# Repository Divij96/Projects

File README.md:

# Projects
## ROS project avalanche rescue
### Search and Rescue avalanche scenario (Mission), Autonomous Systems
- The project was implemented in C++ using ROS packages. Visualization was done in Unity environment and Rviz. <br />

Task: fly over the avalanche and locate victims. Work packages included:- <br />
-  realistic sensor models for avalanche beacon (noise & capabilities)
-  mission planning
-  adaptive trajectory generation
-  location report

## Scara Robot
### Design and build-up of a 4 DoF SCARA like robot (3+1gripper), Intelligent machine design lab
- Mechanical models were designed using Autodesk inventor and built using 3dprinters
- The PCBs were designed using the Autodesk Eagle. They were later on manufactured
and soldered
- Each joint had an Absolute position encoder, a Torque sensor, a BLDC motor, a
gearbox, and a pair of Cross-Roller-Bearings. A master Linux PC with EtherCAT was
used for communication with the joint slaves
- The low-level control was implemented on the Microcontroller chip using C. A highlevel
control was implemented in MATLAB. EtherLab was used as a communication
interface
- The CDTM (Center for Digital Technology Management) supported us regarding the
team communication and project management aspects

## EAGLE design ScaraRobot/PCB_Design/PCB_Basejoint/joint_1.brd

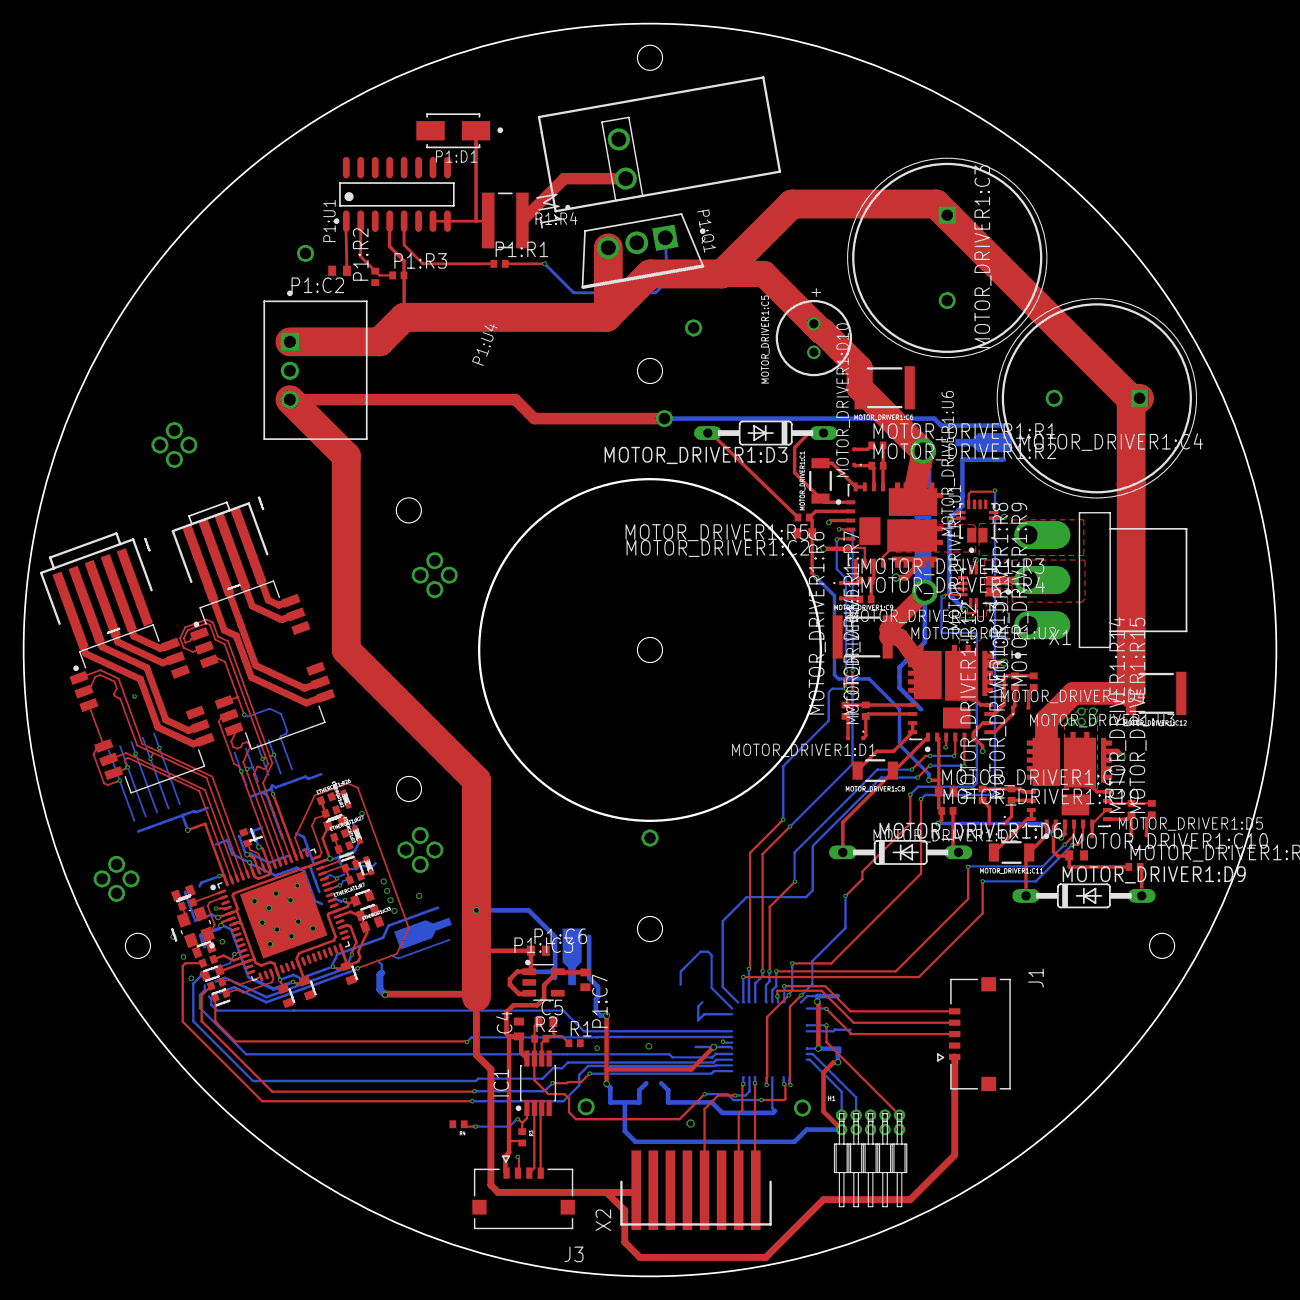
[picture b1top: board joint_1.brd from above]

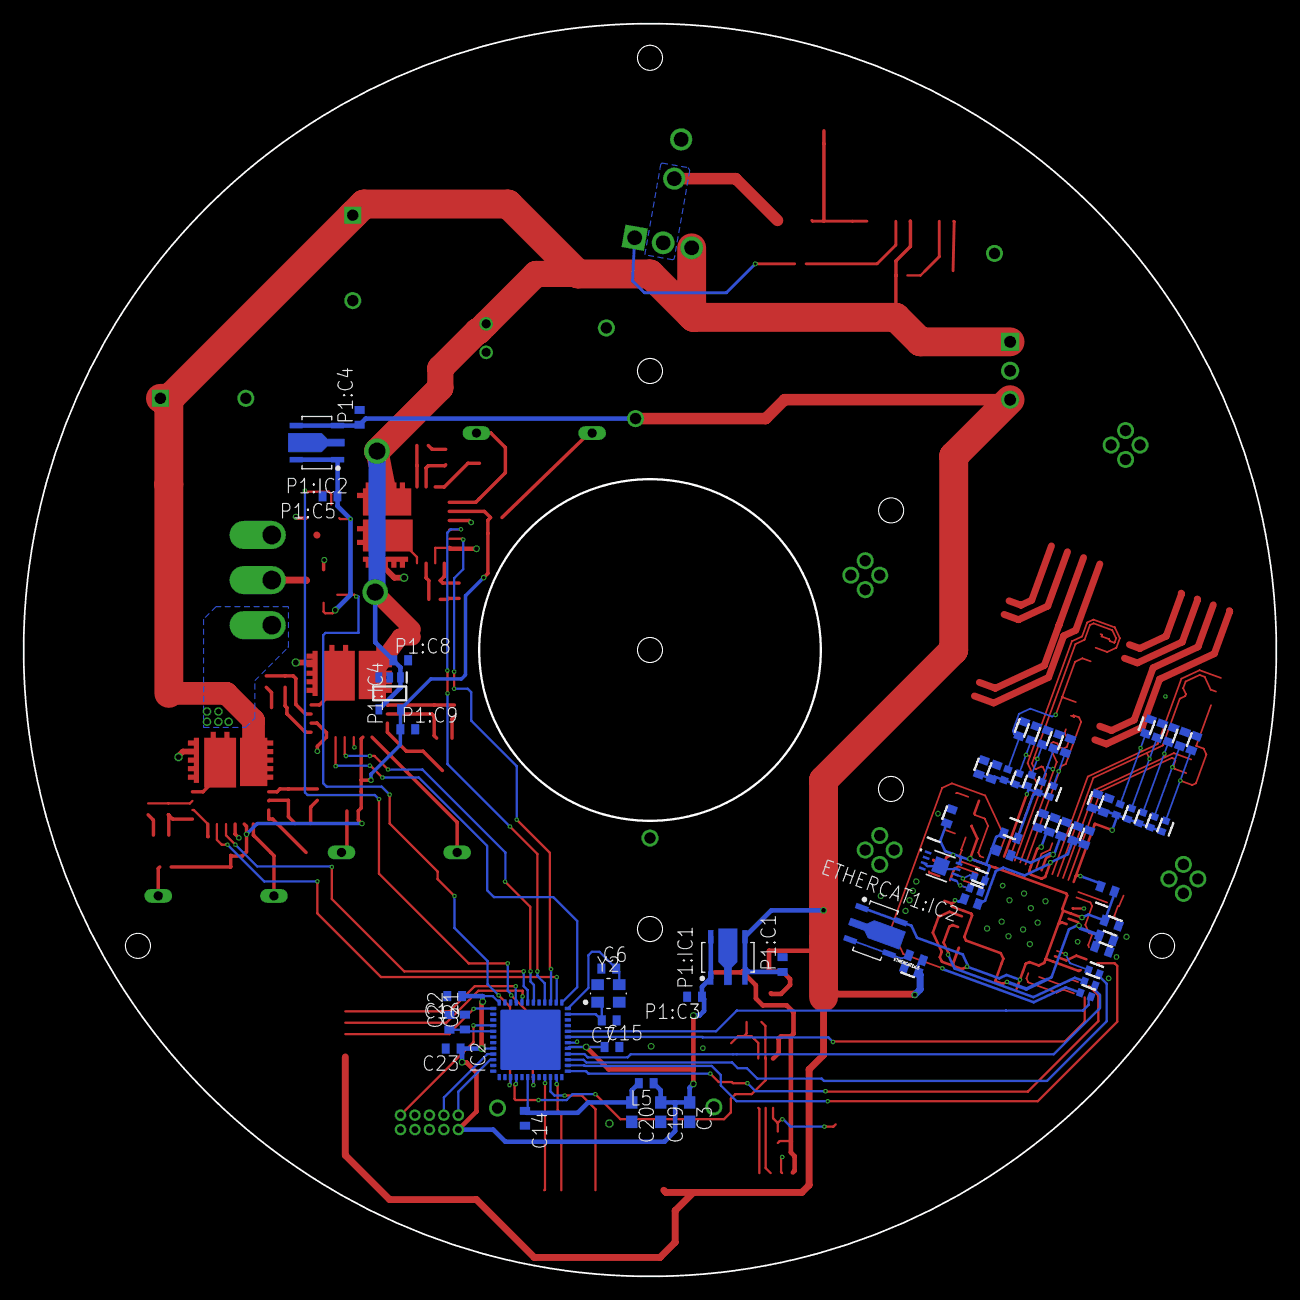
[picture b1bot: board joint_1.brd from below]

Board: 2 copper layers, 110.0 x 110.0 mm, 166 parts (69 on the bottom side), 120 nets.

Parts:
C3, C19, C20: 10uF/10V; C0603
C4, C14, C15, C16, C23: 100nF; C0402
C5: GCM1555C1H102FA16; C0402
C6, C7: GCM1555C1H100JA16; C0402
C21: GCM155R71C104JA55; C0402
C22: GRM155C80J475MEAAD; C0402
ETHERCAT1:C1, ETHERCAT1:C3, ETHERCAT1:C6, ETHERCAT1:C8, ETHERCAT1:C16: 1u; C0402
ETHERCAT1:C2, ETHERCAT1:C4, ETHERCAT1:C5, ETHERCAT1:C7, ETHERCAT1:C9, ETHERCAT1:C10, ETHERCAT1:C11, ETHERCAT1:C12, ETHERCAT1:C13, ETHERCAT1:C14, ETHERCAT1:C15, ETHERCAT1:C18, ETHERCAT1:C19, ETHERCAT1:C22: 100n; C0402
ETHERCAT1:C17: 470p; C0402
ETHERCAT1:C20, ETHERCAT1:C21: 18p; C0402
ETHERCAT1:C23, ETHERCAT1:C24, ETHERCAT1:C25, ETHERCAT1:C26, ETHERCAT1:C27, ETHERCAT1:C28, ETHERCAT1:C29, ETHERCAT1:C30: GCM1555C1H100JA16; C0402
ETHERCAT1:C31, ETHERCAT1:C32: 22n; C0402
ETHERCAT1:C33: GRM155C80J106ME11D; C0402
ETHERCAT1:C66: 1uF; C0402
ETHERCAT1:D1, ETHERCAT1:D2, ETHERCAT1:D3: QBLP595-IG; LED0402
ETHERCAT1:IC1: CAT24C512IGT3HU5; UDFN8
ETHERCAT1:IC2: RP115H331B-T1-FE; SOT-89-5
ETHERCAT1:L1, ETHERCAT1:L2, ETHERCAT1:L3, ETHERCAT1:L4, ETHERCAT1:L5: BLM15EG221SH1D; BEAD0402
ETHERCAT1:R1, ETHERCAT1:R16, ETHERCAT1:R17: 0R; R0402
ETHERCAT1:R2: 12k1; R0402
ETHERCAT1:R4, ETHERCAT1:R5: 4k7; R0402
ETHERCAT1:R6, ETHERCAT1:R24, ETHERCAT1:R25: 10k; R0402
ETHERCAT1:R7, ETHERCAT1:R26, ETHERCAT1:R27: RL0402FR-7W10KL; R0402
ETHERCAT1:R8, ETHERCAT1:R9, ETHERCAT1:R10, ETHERCAT1:R11, ETHERCAT1:R12, ETHERCAT1:R13, ETHERCAT1:R14, ETHERCAT1:R15: 49R9; R0402
ETHERCAT1:R18, ETHERCAT1:R19, ETHERCAT1:R20, ETHERCAT1:R21, ETHERCAT1:R22, ETHERCAT1:R23: 100; R0402
ETHERCAT1:T1, ETHERCAT1:T2: 749020100; SOIC127P965X533-16-TRAFO
ETHERCAT1:U1: LAN9252/ML; QFN64-T600
ETHERCAT1:X1: 87438-0443; 87438-04
ETHERCAT1:X3: 87438-0543; 87438-05
ETHERCAT1:Y1: ECX-2236
H1: 20021112-00010T4LF; 20021112-00010
IC1: MAX4208AUA+T; USOP8
IC2: ATSAMD51G18A-MUT; QFN48
J1: 5037630591; MOLEX_5037630591
J3: 5037630491; MOLEX_5037630491
L5: BLM15EG221SH1D; BEAD0402
M1: PST1,3/2-3,5; 1945096
MOTOR_DRIVER1:C1, MOTOR_DRIVER1:C8, MOTOR_DRIVER1:C11: 10 µF; WCAP-CSGP_1206_H1.6
MOTOR_DRIVER1:C2, MOTOR_DRIVER1:C7, MOTOR_DRIVER1:C10: 10u 25V; C0402
MOTOR_DRIVER1:C3, MOTOR_DRIVER1:C4: MAL219091105E3; CAPPRD750W80D1650H2700
MOTOR_DRIVER1:C5: 220 µF; WCAP-ATG8_6.3X11(DXL)
MOTOR_DRIVER1:C6, MOTOR_DRIVER1:C9, MOTOR_DRIVER1:C12: 470000pF; WCAP-CSMH_1812_H2.0
MOTOR_DRIVER1:D1, MOTOR_DRIVER1:D2, MOTOR_DRIVER1:D4, MOTOR_DRIVER1:D5, MOTOR_DRIVER1:D10, MOTOR_DRIVER1:D11: INFINEON_BAS3005A-02VINFINEON_BAS3005A-02V_0_0; INFINEON_BAS3005A-02V_0
MOTOR_DRIVER1:D3, MOTOR_DRIVER1:D6, MOTOR_DRIVER1:D9: BAV21; DO35-10
MOTOR_DRIVER1:R1, MOTOR_DRIVER1:R4, MOTOR_DRIVER1:R6, MOTOR_DRIVER1:R9, MOTOR_DRIVER1:R12, MOTOR_DRIVER1:R15: 27; R0402
MOTOR_DRIVER1:R2, MOTOR_DRIVER1:R3, MOTOR_DRIVER1:R7, MOTOR_DRIVER1:R8, MOTOR_DRIVER1:R13, MOTOR_DRIVER1:R14: 100; R0402
MOTOR_DRIVER1:R5, MOTOR_DRIVER1:R10, MOTOR_DRIVER1:R16: 5.1; R0402
MOTOR_DRIVER1:U1, MOTOR_DRIVER1:U2, MOTOR_DRIVER1:U3: IRSM005-800MHINFINEON_IRSM005-800MH_0_0; INFINEON_IRSM005-800MH_0
MOTOR_DRIVER1:U6, MOTOR_DRIVER1:U7: ALLEGRO_MICROSYSTEMS_LLC_ACS70331EESATR-005B3ALLE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; ALLEGRO_MICROSYSTEMS_LLC_ACS70331EESATR-005B3_0
P1:C1, P1:C3, P1:C4, P1:C5, P1:C6, P1:C8, P1:C9: GCM155C71A105KE38D; C0402
P1:C2: GCM155R71C104JA55; C0402
P1:C7: GRM155C80J225KE95D; C0402
P1:D1: DIODES_SMAT70A-13-FDIODES_SMAT70A-13-F_0_0; DIODES_SMAT70A-13-F_0
P1:IC1, P1:IC2: RP115H331B-T1-FE; SOT-89-5
P1:IC3: AP2204K-5.0TRG1; SOT-23-5
P1:IC4: XC6701AF02MR-G; SOT95P280X130-5N
P1:Q1: INFINEON_IRF640NPBFINFINEON_IRF640NPBF_0_0; INFINEON_IRF640NPBF_0
P1:R1: 10; R0402
P1:R2: 4.99k; R0402
P1:R3: 118k; R0402
P1:R4: VISHAY_CRCW12181K00FKEKVISHAY_CRCW12181K00FKEK_0_0; VISHAY_CRCW12181K00FKEK_0
P1:U1: LINEAR_TECHNOLOGY_LT4356HS-3#PBFLINEAR_TECHNOLOGY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; LINEAR_TECHNOLOGY_LT4356HS-3#PBF_0
P1:U4: RECOM_R-78E5.0-1.0RECOM_R-78E5.0-1.0_0_0; RECOM_R-78E5.0-1.0_0
R1: Rg; R0402
R2: Rg2; R0402
R3, R4: RT0402FRE07100KL; R0402
U$1: PTDA1,5/2-PH-3,5; 1725107
X1: B3PS-VH(LF)(SN)
X2: 87438-0843; 87438-08
Y2: ECX-2236

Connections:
3V3_CURRENT: MOTOR_DRIVER1:U6.12, MOTOR_DRIVER1:U7.12, P1:C5.1, P1:IC2.1, P1:IC2.5
3V3_MICRO: C3.1, C15.1, C16.1, C19.1, C23.1, H1.1, IC2.17, IC2.36, IC2.44, L5.1, P1:C3.1, P1:IC1.1, P1:IC1.5
5V_TORQUE: C4.1, IC1.8, J3.1, P1:C7.1, P1:IC3.5, R3.2
+5V: ETHERCAT1:C66.1, ETHERCAT1:L5.1, J1.1, P1:C1.1, P1:C4.1, P1:C6.1, P1:IC1.3, P1:IC1.4, P1:IC2.3, P1:IC2.4, P1:IC3.1, P1:IC3.3, P1:U4.3, X2.1
+15V: MOTOR_DRIVER1:C2.1, MOTOR_DRIVER1:C7.1, MOTOR_DRIVER1:C10.1, MOTOR_DRIVER1:R5.1, MOTOR_DRIVER1:R10.1, MOTOR_DRIVER1:R16.1, MOTOR_DRIVER1:U1.2, MOTOR_DRIVER1:U2.2, MOTOR_DRIVER1:U3.2, P1:C9.1, P1:IC4.5
+24V: MOTOR_DRIVER1:C3.1, MOTOR_DRIVER1:C4.1, MOTOR_DRIVER1:C5.1, MOTOR_DRIVER1:C6.2, MOTOR_DRIVER1:C9.2, MOTOR_DRIVER1:C12.2, MOTOR_DRIVER1:U1.18-19-20-21-22-23, MOTOR_DRIVER1:U2.18-19-20-21-22-23, MOTOR_DRIVER1:U3.18-19-20-21-22-23, P1:C8.1, P1:IC4.1, P1:IC4.4, P1:Q1.3, P1:R3.2, P1:U1.4, P1:U4.1
CURRENT_A: IC2.3, MOTOR_DRIVER1:U7.10
CURRENT_B: IC2.7, MOTOR_DRIVER1:U6.10
ECAT_CS: ETHERCAT1:R19.2, IC2.20
ECAT_DATA2: ETHERCAT1:R21.2, IC2.15
ECAT_DATA3: ETHERCAT1:R20.2, IC2.16
ECAT_MISO: ETHERCAT1:R22.2, IC2.14
ECAT_MOSI: ETHERCAT1:R23.2, IC2.13
ECAT_SCK: ETHERCAT1:R18.2, IC2.19
ENA: IC2.27, MOTOR_DRIVER1:U1.5
ENB: IC2.25, MOTOR_DRIVER1:U2.5
ENC: IC2.26, MOTOR_DRIVER1:U3.5
ETHERCAT1:#MISO: ETHERCAT1:R22.1, ETHERCAT1:U1.13
ETHERCAT1:#MOSI: ETHERCAT1:R23.1, ETHERCAT1:U1.17
ETHERCAT1:#SCK: ETHERCAT1:R18.1, ETHERCAT1:U1.19
ETHERCAT1:#SCS#: ETHERCAT1:R19.1, ETHERCAT1:U1.50
ETHERCAT1:#SQI2: ETHERCAT1:R21.1, ETHERCAT1:U1.12
ETHERCAT1:#SQI3: ETHERCAT1:R20.1, ETHERCAT1:U1.35
ETHERCAT1:+3V3: ETHERCAT1:C10.1, ETHERCAT1:C11.1, ETHERCAT1:C12.1, ETHERCAT1:C13.1, ETHERCAT1:C14.1, ETHERCAT1:C15.1, ETHERCAT1:C22.1, ETHERCAT1:C33.1, ETHERCAT1:D1.2, ETHERCAT1:IC1.8, ETHERCAT1:IC2.1, ETHERCAT1:IC2.5, ETHERCAT1:L1.1, ETHERCAT1:L2.1, ETHERCAT1:L3.1, ETHERCAT1:R4.2, ETHERCAT1:R5.2, ETHERCAT1:R6.2, ETHERCAT1:U1.5, ETHERCAT1:U1.7, ETHERCAT1:U1.14, ETHERCAT1:U1.20, ETHERCAT1:U1.32, ETHERCAT1:U1.37, ETHERCAT1:U1.47
ETHERCAT1:CT1: ETHERCAT1:C31.1, ETHERCAT1:R16.1, ETHERCAT1:T1.3, ETHERCAT1:T1.6
ETHERCAT1:CT2: ETHERCAT1:C32.1, ETHERCAT1:R17.1, ETHERCAT1:T2.3, ETHERCAT1:T2.6
ETHERCAT1:GPIO0: ETHERCAT1:R24.2, ETHERCAT1:R26.1, ETHERCAT1:U1.48
ETHERCAT1:GPIO1: ETHERCAT1:R25.2, ETHERCAT1:R27.1, ETHERCAT1:U1.46
ETHERCAT1:GPIO2: ETHERCAT1:R6.1, ETHERCAT1:R7.2, ETHERCAT1:U1.45
ETHERCAT1:I2C_SCL: ETHERCAT1:IC1.6, ETHERCAT1:R4.1, ETHERCAT1:U1.43
ETHERCAT1:I2C_SDA: ETHERCAT1:IC1.5, ETHERCAT1:R5.1, ETHERCAT1:U1.42
ETHERCAT1:IN_RX_N: ETHERCAT1:T1.9, ETHERCAT1:X1.4
ETHERCAT1:IN_RX_P: ETHERCAT1:T1.10, ETHERCAT1:X1.3
ETHERCAT1:IN_TX_N: ETHERCAT1:T1.15, ETHERCAT1:X1.2
ETHERCAT1:IN_TX_P: ETHERCAT1:T1.16, ETHERCAT1:X1.1
ETHERCAT1:N$1: ETHERCAT1:D2.2, ETHERCAT1:R26.2
ETHERCAT1:N$2: ETHERCAT1:D3.2, ETHERCAT1:R27.2
ETHERCAT1:N$3: ETHERCAT1:IC2.3, ETHERCAT1:IC2.4, ETHERCAT1:L5.2
ETHERCAT1:N$15: ETHERCAT1:D1.1, ETHERCAT1:R7.1
ETHERCAT1:OSCI: ETHERCAT1:R1.2, ETHERCAT1:U1.1
ETHERCAT1:OSCI1: ETHERCAT1:C20.2, ETHERCAT1:R1.1, ETHERCAT1:Y1.3
ETHERCAT1:OSCO: ETHERCAT1:C21.2, ETHERCAT1:U1.2, ETHERCAT1:Y1.1
ETHERCAT1:OUT_RX_N: ETHERCAT1:T2.9, ETHERCAT1:X3.5
ETHERCAT1:OUT_RX_P: ETHERCAT1:T2.10, ETHERCAT1:X3.4
ETHERCAT1:OUT_TX_N: ETHERCAT1:T2.15, ETHERCAT1:X3.3
ETHERCAT1:OUT_TX_P: ETHERCAT1:T2.16, ETHERCAT1:X3.2
ETHERCAT1:RBIAS: ETHERCAT1:R2.2, ETHERCAT1:U1.57
ETHERCAT1:RXA_N: ETHERCAT1:C24.1, ETHERCAT1:R10.1, ETHERCAT1:T1.8, ETHERCAT1:U1.54
ETHERCAT1:RXA_P: ETHERCAT1:C23.1, ETHERCAT1:R11.1, ETHERCAT1:T1.7, ETHERCAT1:U1.55
ETHERCAT1:RXB_N: ETHERCAT1:C28.1, ETHERCAT1:R14.1, ETHERCAT1:T2.2, ETHERCAT1:U1.61
ETHERCAT1:RXB_P: ETHERCAT1:C27.1, ETHERCAT1:R15.1, ETHERCAT1:T2.1, ETHERCAT1:U1.60
ETHERCAT1:TXA_N: ETHERCAT1:C26.1, ETHERCAT1:R8.1, ETHERCAT1:T1.2, ETHERCAT1:U1.52
ETHERCAT1:TXA_P: ETHERCAT1:C25.1, ETHERCAT1:R9.1, ETHERCAT1:T1.1, ETHERCAT1:U1.53
ETHERCAT1:TXB_N: ETHERCAT1:C30.1, ETHERCAT1:R12.1, ETHERCAT1:T2.8, ETHERCAT1:U1.63
ETHERCAT1:TXB_P: ETHERCAT1:C29.1, ETHERCAT1:R13.1, ETHERCAT1:T2.7, ETHERCAT1:U1.62
ETHERCAT1:VDD: ETHERCAT1:C16.1, ETHERCAT1:C17.1, ETHERCAT1:C18.1, ETHERCAT1:C19.1, ETHERCAT1:L4.1, ETHERCAT1:U1.6, ETHERCAT1:U1.24, ETHERCAT1:U1.38
ETHERCAT1:VDD12TX: ETHERCAT1:C6.1, ETHERCAT1:C7.1, ETHERCAT1:C8.1, ETHERCAT1:C9.1, ETHERCAT1:L4.2, ETHERCAT1:U1.56, ETHERCAT1:U1.59
ETHERCAT1:VDD33BIAS: ETHERCAT1:C5.1, ETHERCAT1:L3.2, ETHERCAT1:U1.58
ETHERCAT1:VDD33TXRX1: ETHERCAT1:C1.1, ETHERCAT1:C2.1, ETHERCAT1:L1.2, ETHERCAT1:R8.2, ETHERCAT1:R9.2, ETHERCAT1:R10.2, ETHERCAT1:R11.2, ETHERCAT1:R16.2, ETHERCAT1:U1.51
ETHERCAT1:VDD33TXRX2: ETHERCAT1:C3.1, ETHERCAT1:C4.1, ETHERCAT1:L2.2, ETHERCAT1:R12.2, ETHERCAT1:R13.2, ETHERCAT1:R14.2, ETHERCAT1:R15.2, ETHERCAT1:R17.2, ETHERCAT1:U1.64
GND: C3.2, C4.2, C6.1, C7.1, C14.2, C15.2, C16.2, C19.2, C20.2, C21.2, C22.2, C23.2, ETHERCAT1:C1.2, ETHERCAT1:C2.2, ETHERCAT1:C3.2, ETHERCAT1:C4.2, ETHERCAT1:C5.2, ETHERCAT1:C6.2, ETHERCAT1:C7.2, ETHERCAT1:C8.2, ETHERCAT1:C9.2, ETHERCAT1:C10.2, ETHERCAT1:C11.2, ETHERCAT1:C12.2, ETHERCAT1:C13.2, ETHERCAT1:C14.2, ETHERCAT1:C15.2, ETHERCAT1:C16.2, ETHERCAT1:C17.2, ETHERCAT1:C18.2, ETHERCAT1:C19.2, ETHERCAT1:C20.1, ETHERCAT1:C21.1, ETHERCAT1:C22.2, ETHERCAT1:C23.2, ETHERCAT1:C24.2, ETHERCAT1:C25.2, ETHERCAT1:C26.2, ETHERCAT1:C27.2, ETHERCAT1:C28.2, ETHERCAT1:C29.2, ETHERCAT1:C30.2, ETHERCAT1:C31.2, ETHERCAT1:C32.2, ETHERCAT1:C33.2, ETHERCAT1:C66.2, ETHERCAT1:D2.1, ETHERCAT1:D3.1, ETHERCAT1:IC1.1, ETHERCAT1:IC1.2, ETHERCAT1:IC1.3, ETHERCAT1:IC1.4, ETHERCAT1:IC1.7, ETHERCAT1:IC1.9, ETHERCAT1:IC2.2, ETHERCAT1:R2.1, ETHERCAT1:R24.1, ETHERCAT1:R25.1, ETHERCAT1:U1.4, ETHERCAT1:U1.8, ETHERCAT1:U1.9, ETHERCAT1:U1.10, ETHERCAT1:U1.41, ETHERCAT1:U1.65, ETHERCAT1:Y1.2, ETHERCAT1:Y1.4, H1.3, H1.5, IC1.4, IC1.5, IC2.5, IC2.18, IC2.35, IC2.42, J1.2, J3.2, M1.2, MOTOR_DRIVER1:C2.2, MOTOR_DRIVER1:C3.2, MOTOR_DRIVER1:C4.2, MOTOR_DRIVER1:C5.2, MOTOR_DRIVER1:C6.1, MOTOR_DRIVER1:C7.2, MOTOR_DRIVER1:C9.1, MOTOR_DRIVER1:C10.2, MOTOR_DRIVER1:C12.1, MOTOR_DRIVER1:U1.3, MOTOR_DRIVER1:U1.6, MOTOR_DRIVER1:U1.8, MOTOR_DRIVER1:U1.11-12-13-14-15, MOTOR_DRIVER1:U2.3, MOTOR_DRIVER1:U2.6, MOTOR_DRIVER1:U2.8, MOTOR_DRIVER1:U2.11-12-13-14-15, MOTOR_DRIVER1:U3.3, MOTOR_DRIVER1:U3.6, MOTOR_DRIVER1:U3.8, MOTOR_DRIVER1:U3.11-12-13-14-15, MOTOR_DRIVER1:U6.5, MOTOR_DRIVER1:U7.5, P1:C1.2, P1:C2.2, P1:C3.2, P1:C4.2, P1:C5.2, P1:C6.2, P1:C7.2, P1:C8.2, P1:C9.2, P1:D1.2, P1:IC1.2, P1:IC2.2, P1:IC3.2, P1:IC4.2, P1:R2.1, P1:U1.12, P1:U4.2, R1.2, R4.2, X2.2, Y2.2, Y2.4
HALL_A: IC2.33, J1.5
HALL_B: IC2.32, J1.4
HALL_C: IC2.37, J1.3
INA: IC2.28, MOTOR_DRIVER1:U1.4
INB: IC2.30, MOTOR_DRIVER1:U2.4
INC: IC2.31, MOTOR_DRIVER1:U3.4
MOTOR_DRIVER1:N$1: MOTOR_DRIVER1:R1.2, MOTOR_DRIVER1:R2.2, MOTOR_DRIVER1:U1.24
MOTOR_DRIVER1:N$2: MOTOR_DRIVER1:D10.2, MOTOR_DRIVER1:R1.1
MOTOR_DRIVER1:N$3: MOTOR_DRIVER1:D10.1, MOTOR_DRIVER1:R2.1, MOTOR_DRIVER1:U1.25
MOTOR_DRIVER1:N$4: MOTOR_DRIVER1:R6.2, MOTOR_DRIVER1:R7.2, MOTOR_DRIVER1:U2.24
MOTOR_DRIVER1:N$5: MOTOR_DRIVER1:R3.2, MOTOR_DRIVER1:R4.2, MOTOR_DRIVER1:U1.9
MOTOR_DRIVER1:N$6: MOTOR_DRIVER1:D11.2, MOTOR_DRIVER1:R4.1
MOTOR_DRIVER1:N$7: MOTOR_DRIVER1:D11.1, MOTOR_DRIVER1:R3.1, MOTOR_DRIVER1:U1.7
MOTOR_DRIVER1:N$8: MOTOR_DRIVER1:C1.2, MOTOR_DRIVER1:U1.26, MOTOR_DRIVER1:U1.27
MOTOR_DRIVER1:N$9: MOTOR_DRIVER1:C1.1, MOTOR_DRIVER1:D3.C, MOTOR_DRIVER1:U1.1
MOTOR_DRIVER1:N$10: MOTOR_DRIVER1:D3.A, MOTOR_DRIVER1:R5.2
MOTOR_DRIVER1:N$12: MOTOR_DRIVER1:D1.2, MOTOR_DRIVER1:R6.1
MOTOR_DRIVER1:N$13: MOTOR_DRIVER1:D1.1, MOTOR_DRIVER1:R7.1, MOTOR_DRIVER1:U2.25
MOTOR_DRIVER1:N$14: MOTOR_DRIVER1:R8.2, MOTOR_DRIVER1:R9.2, MOTOR_DRIVER1:U2.9
MOTOR_DRIVER1:N$15: MOTOR_DRIVER1:D4.2, MOTOR_DRIVER1:R9.1
MOTOR_DRIVER1:N$16: MOTOR_DRIVER1:D4.1, MOTOR_DRIVER1:R8.1, MOTOR_DRIVER1:U2.7
MOTOR_DRIVER1:N$17: MOTOR_DRIVER1:C8.2, MOTOR_DRIVER1:U2.26, MOTOR_DRIVER1:U2.27
MOTOR_DRIVER1:N$18: MOTOR_DRIVER1:C8.1, MOTOR_DRIVER1:D6.C, MOTOR_DRIVER1:U2.1
MOTOR_DRIVER1:N$19: MOTOR_DRIVER1:D6.A, MOTOR_DRIVER1:R10.2
MOTOR_DRIVER1:N$21: MOTOR_DRIVER1:R12.2, MOTOR_DRIVER1:R13.2, MOTOR_DRIVER1:U3.24
MOTOR_DRIVER1:N$22: MOTOR_DRIVER1:D2.2, MOTOR_DRIVER1:R12.1
MOTOR_DRIVER1:N$23: MOTOR_DRIVER1:D2.1, MOTOR_DRIVER1:R13.1, MOTOR_DRIVER1:U3.25
MOTOR_DRIVER1:N$24: MOTOR_DRIVER1:R14.2, MOTOR_DRIVER1:R15.2, MOTOR_DRIVER1:U3.9
MOTOR_DRIVER1:N$25: MOTOR_DRIVER1:D5.2, MOTOR_DRIVER1:R15.1
MOTOR_DRIVER1:N$26: MOTOR_DRIVER1:D5.1, MOTOR_DRIVER1:R14.1, MOTOR_DRIVER1:U3.7
MOTOR_DRIVER1:N$27: MOTOR_DRIVER1:C11.2, MOTOR_DRIVER1:U3.26, MOTOR_DRIVER1:U3.27
MOTOR_DRIVER1:N$28: MOTOR_DRIVER1:C11.1, MOTOR_DRIVER1:D9.C, MOTOR_DRIVER1:U3.1
MOTOR_DRIVER1:N$29: MOTOR_DRIVER1:D9.A, MOTOR_DRIVER1:R16.2
MOTOR_DRIVER1:U1: MOTOR_DRIVER1:U1.10, MOTOR_DRIVER1:U1.16-17, MOTOR_DRIVER1:U6.1-2
MOTOR_DRIVER1:V1: MOTOR_DRIVER1:U2.10, MOTOR_DRIVER1:U2.16-17, MOTOR_DRIVER1:U7.1-2
unnamed: C5.2, IC1.6, R1.1, R2.2
unnamed: IC1.1, R3.1, R4.1
NRESET: H1.10, IC2.40
P1:FB_LT4356: P1:R2.2, P1:R3.1, P1:U1.2
P1:N$1: P1:R1.1, P1:U1.5
P1:N$2: P1:Q1.1, P1:R1.2
P1:N$5: P1:C2.1, P1:U1.1
P1:VCC/SNS_LT4356: P1:D1.1, P1:R4.1, P1:U1.7, P1:U1.8
POS_MISO: IC2.11, X2.7
POS_MOSI: IC2.9, X2.8
POS_SCK: IC2.10, X2.5
SWCLK: H1.4, IC2.45
SWDIO: H1.2, IC2.46
TORQUE_SENS: C5.1, IC1.7, IC2.4, R2.1
U: MOTOR_DRIVER1:U6.3-4, X1.3
UD+: IC1.3, J3.4
UD-: IC1.2, J3.3
V: MOTOR_DRIVER1:U7.3-4, X1.2
VDDANA: C14.1, C20.1, IC2.6, L5.2
VDDCORE: C21.1, C22.1, IC2.41
VIN: M1.1, P1:Q1.2, P1:R4.2
W: MOTOR_DRIVER1:U3.10, MOTOR_DRIVER1:U3.16-17, X1.1
XIN: C7.2, IC2.23, Y2.1
XOUT: C6.2, IC2.24, Y2.3

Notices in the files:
parts and their libraries:
Wurth_Capacitors_WCAP-ATG8: Copyright: Würth Elektronik
